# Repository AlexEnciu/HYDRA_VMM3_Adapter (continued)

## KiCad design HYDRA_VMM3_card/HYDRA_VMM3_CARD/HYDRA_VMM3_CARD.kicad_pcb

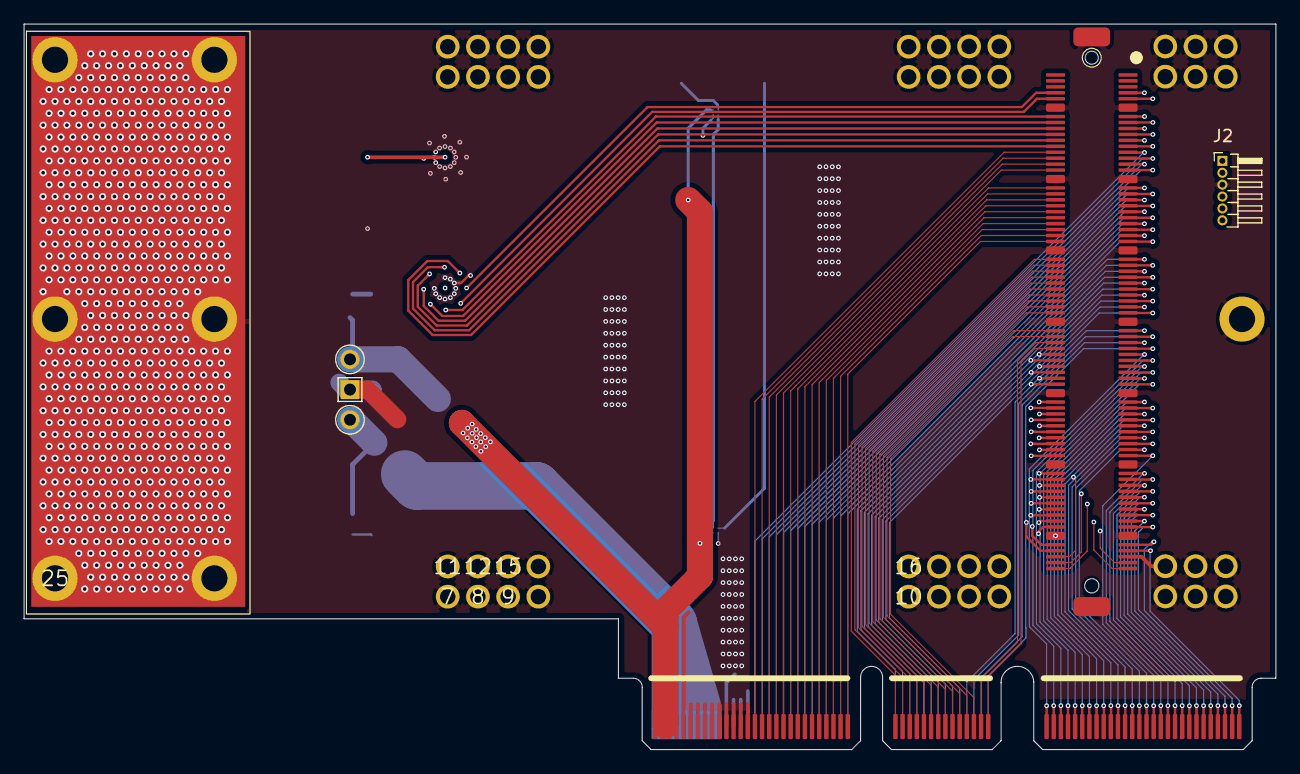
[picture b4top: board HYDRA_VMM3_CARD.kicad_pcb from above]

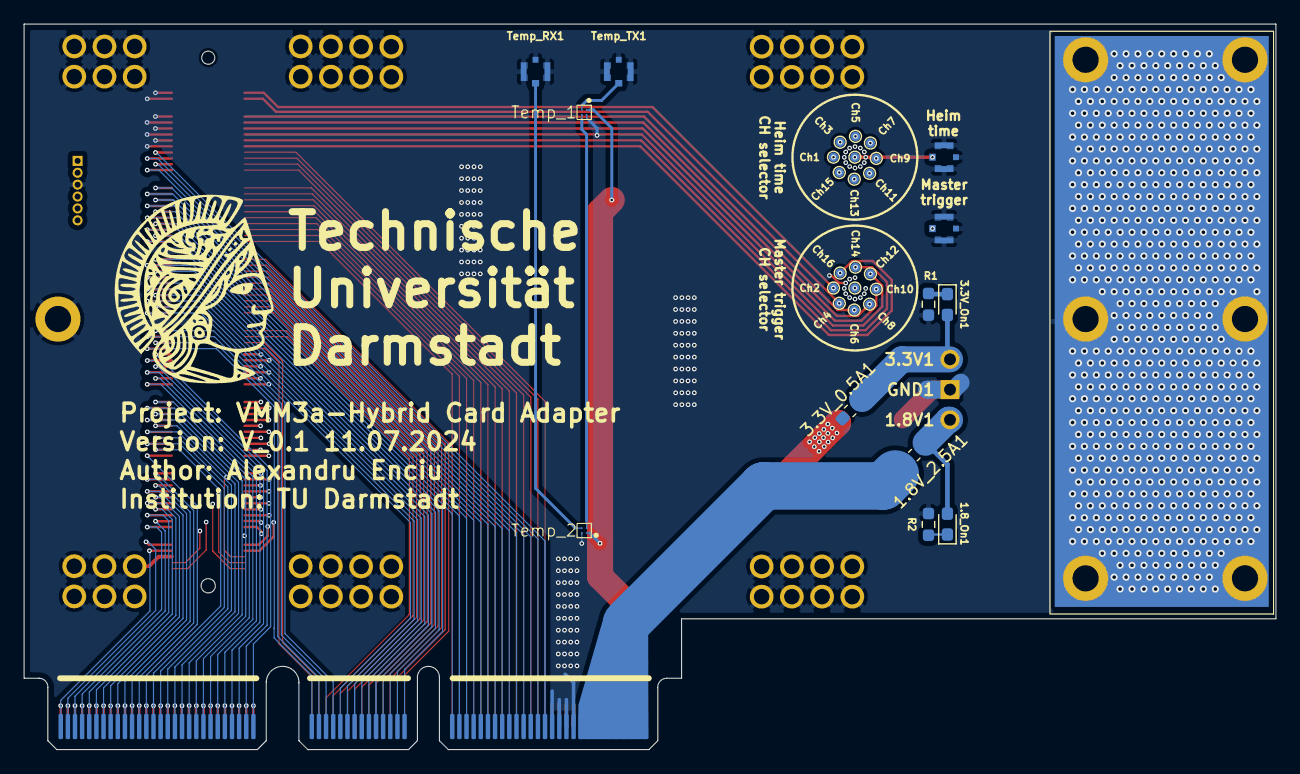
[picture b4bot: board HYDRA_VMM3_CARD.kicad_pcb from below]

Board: 6 copper layers, 105.3 x 61.0 mm, 61 parts (30 on the bottom side), 145 nets.

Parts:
1, 2, 3, 4, 5, 6, 7, 8, 9, 10, 11, 12, 13, 14, 15, 16, 17, 18, 19, 20, 21, 22, 23, 24, 25: (no value)
1.8V1: 1.8V; TestPoint_Pad_D2.5mm
1.8V_2.5A1: 2.5A; Fuse_0603_1608Metric_Pad1.05x0.95mm_HandSolder
1.8_On1, 3.3V_On1: LED; LED_0603_1608Metric_Pad1.05x0.95mm_HandSolder
3.3V1: 3.3V; TestPoint_Pad_D2.5mm
3.3V_0.5A1: 0.5A; Fuse_0603_1608Metric_Pad1.05x0.95mm_HandSolder
Ch1, Ch2, Ch3, Ch4, Ch5, Ch6, Ch7, Ch8, Ch9, Ch10, Ch11, Ch12, Ch13, Ch14, Ch15, Ch16: TestPoint; TestPoint_Pad_D1.0mm
GND1: GND; TestPoint_Pad_2.5x2.5mm
J1: ME1014010101011; Edge-Card-Connector
J2: Conn_01x06_Pin; PinHeader_1x06_P1.00mm_Horizontal
R1, R2: 1k; R_0603_1608Metric_Pad0.98x0.95mm_HandSolder
Sig1, Sig2: 20449-001E-03; IPEX_20449-001E-03
Sig1_selector, Sig2_selector: TestPoint; TestPoint_Pad_D1.0mm
Temp_1, Temp_2: TMP104
Temp_RX1: 20449-001E-03; IPEX_20449-001E-03
Temp_TX1: 20449-001E-03; IPEX_20449-001E-03
U1: Hirose-FX10

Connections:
Ch_1: Ch1.1, U1.7
Ch_2: Ch2.1, U1.8
Ch_3: Ch15.1, U1.9
Ch_4: Ch4.1, U1.10
Ch_5: Ch13.1, U1.11
Ch_6: Ch6.1, U1.12
Ch_7: Ch11.1, U1.13
Ch_8: Ch8.1, U1.14
Ch_9: Ch9.1, U1.15
Ch_10: Ch10.1, U1.16
Ch_11: Ch7.1, U1.17
Ch_12: Ch12.1, U1.18
Ch_13: Ch5.1, U1.19
Ch_14: Ch14.1, U1.20
Ch_15: Ch3.1, U1.21
Ch_16: Ch16.1, U1.22
Ch_17: J1.A15, U1.23
Ch_18: J1.B15, U1.24
Ch_19: J1.A16, U1.25
Ch_20: J1.B16, U1.26
Ch_21: J1.A17, U1.27
Ch_22: J1.B17, U1.28
Ch_23: J1.A18, U1.29
Ch_24: J1.B18, U1.30
Ch_25: J1.A19, U1.31
Ch_26: J1.B19, U1.32
Ch_27: J1.A20, U1.33
Ch_28: J1.B20, U1.34
Ch_29: J1.A21, U1.35
Ch_30: J1.B21, U1.36
Ch_31: J1.A22, U1.37
Ch_32: J1.B22, U1.38
Ch_33: J1.A23, U1.39
Ch_34: J1.B23, U1.40
Ch_35: J1.A24, U1.41
Ch_36: J1.B24, U1.42
Ch_37: J1.A25, U1.43
Ch_38: J1.B25, U1.44
Ch_39: J1.A26, U1.45
Ch_40: J1.B26, U1.46
Ch_41: J1.A27, U1.47
Ch_42: J1.B27, U1.48
Ch_43: J1.A28, U1.49
Ch_44: J1.B28, U1.50
Ch_45: J1.A29, U1.51
Ch_46: J1.B29, U1.52
Ch_47: J1.A30, U1.53
Ch_48: J1.B30, U1.54
Ch_49: J1.A31, U1.55
Ch_50: J1.B31, U1.56
Ch_51: J1.A32, U1.57
Ch_52: J1.B32, U1.58
Ch_53: J1.A33, U1.59
Ch_54: J1.B33, U1.60
Ch_55: J1.A34, U1.61
Ch_56: J1.B34, U1.62
Ch_57: J1.A35, U1.63
Ch_58: J1.B35, U1.64
Ch_59: J1.A36, U1.65
Ch_60: J1.B36, U1.66
Ch_61: J1.A37, U1.67
Ch_62: J1.B37, U1.68
Ch_63: J1.A38, U1.69
Ch_64: J1.B38, U1.70
Ch_65: J1.A39, U1.71
Ch_66: J1.B39, U1.72
Ch_67: J1.A40, U1.73
Ch_68: J1.B40, U1.74
Ch_69: J1.A41, U1.75
Ch_70: J1.B41, U1.76
Ch_71: J1.A42, U1.77
Ch_72: J1.B42, U1.78
Ch_73: J1.A43, U1.79
Ch_74: J1.B43, U1.80
Ch_75: J1.A44, U1.81
Ch_76: J1.B44, U1.82
Ch_77: J1.A45, U1.83
Ch_78: J1.B45, U1.84
Ch_79: J1.A46, U1.85
Ch_80: J1.B46, U1.86
Ch_81: J1.A47, U1.87
Ch_82: J1.B47, U1.88
Ch_83: J1.A48, U1.89
Ch_84: J1.B48, U1.90
Ch_85: J1.A49, U1.91
Ch_86: J1.B49, U1.92
Ch_87: J1.A50, U1.93
Ch_88: J1.B50, U1.94
Ch_89: J1.A51, U1.95
Ch_90: J1.B51, U1.96
Ch_91: J1.A52, U1.97
Ch_92: J1.B52, U1.98
Ch_93: J1.A53, U1.99
Ch_94: J1.B53, U1.100
Ch_95: J1.A54, U1.101
Ch_96: J1.B54, U1.102
Ch_97: J1.A55, U1.103
Ch_98: J1.B55, U1.104
Ch_99: J1.A56, U1.105
Ch_100: J1.B56, U1.106
Ch_101: J1.A57, U1.107
Ch_102: J1.B57, U1.108
Ch_103: J1.A58, U1.109
Ch_104: J1.B58, U1.110
Ch_105: J1.A59, U1.111
Ch_106: J1.B59, U1.112
Ch_107: J1.A60, U1.113
Ch_108: J1.B70, U1.114
Ch_109: J1.A61, U1.115
Ch_110: J1.B69, U1.116
Ch_111: J1.A62, U1.117
Ch_112: J1.B68, U1.118
Ch_113: J1.A63, U1.119
Ch_114: J1.B67, U1.120
Ch_115: J1.A64, U1.121
Ch_116: J1.B66, U1.122
Ch_117: J1.A65, U1.123
Ch_118: J1.B65, U1.124
Ch_119: J1.A66, U1.125
Ch_120: J1.B64, U1.126
Ch_121: J1.A67, U1.127
Ch_122: J1.B63, U1.128
Ch_123: J1.A68, U1.129
Ch_124: J1.B62, U1.130
Ch_125: J1.A69, U1.131
Ch_126: J1.B61, U1.132
Ch_127: J1.A70, U1.133
Ch_128: J1.B60, U1.134
GND: 1.1, 2.1, 3.1, 4.1, 5.1, 6.1, 7.1, 8.1, 9.1, 10.1, 11.1, 12.1, 13.1, 14.1, 15.1, 16.1, 17.1, 18.1, 19.1, 20.1, 21.1, 22.1, 23.1, 24.1, 25.1, GND1.1, J1.A11, J1.A12, J1.A13, J1.A14, J1.B5, J1.B6, J1.B7, J1.B8, J1.B9, J1.B10, J1.B11, J1.B12, J1.B13, J1.B14, J2.3, R1.2, R2.2, Sig1.2, Sig1.3, Sig1.4, Sig2.2, Sig2.3, Sig2.4, Temp_1.2 (GND), Temp_2.2 (GND), Temp_RX1.2, Temp_RX1.3, Temp_RX1.4, Temp_TX1.2, Temp_TX1.3, Temp_TX1.4, U1.135, U1.141 (GND)
I2C_VCC: J2.1, U1.136
unnamed: 1.8V1.1, 1.8V_2.5A1.2, 1.8_On1.2 (A)
unnamed: 1.8_On1.1 (K), R2.1
unnamed: 3.3V1.1, 3.3V_0.5A1.2, 3.3V_On1.2 (A)
unnamed: 3.3V_On1.1 (K), R1.1
unnamed: Temp_1.4 (RX), Temp_2.3 (TX)
P1: 3.3V_0.5A1.1, J1.B1, J1.B2, J1.B3, J1.B4, Temp_1.1 (V+), Temp_2.1 (V+)
P2: 1.8V_2.5A1.1, J1.A1, J1.A2, J1.A3, J1.A4, J1.A5, J1.A6, J1.A7, J1.A8, J1.A9, J1.A10
RX: Temp_2.4 (RX), Temp_RX1.1
SCL: J2.4, U1.140
SDA: J2.5, U1.139
Sig1: Sig1.1, Sig1_selector.1
Sig2: Sig2.1, Sig2_selector.1
Signal_In: J2.6, U1.137
Signal_Out: J2.2, U1.138
TX: Temp_1.3 (TX), Temp_TX1.1

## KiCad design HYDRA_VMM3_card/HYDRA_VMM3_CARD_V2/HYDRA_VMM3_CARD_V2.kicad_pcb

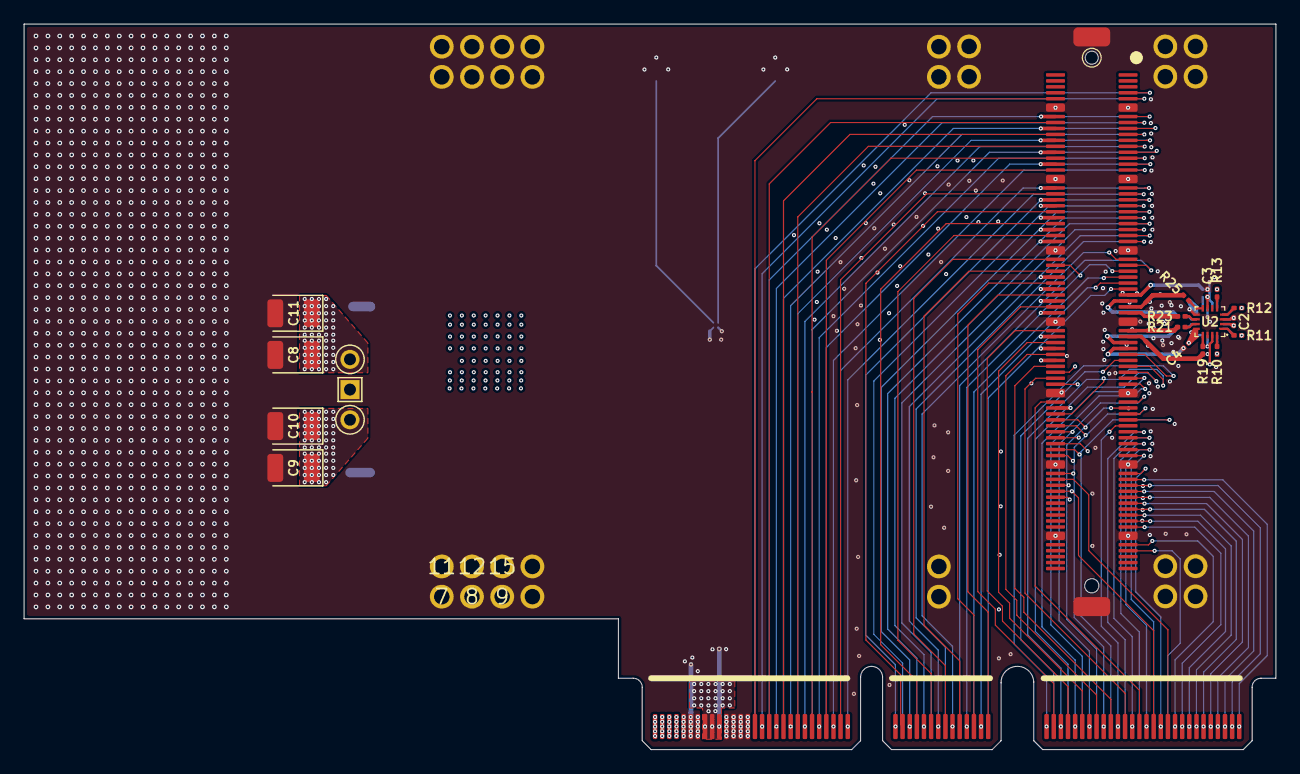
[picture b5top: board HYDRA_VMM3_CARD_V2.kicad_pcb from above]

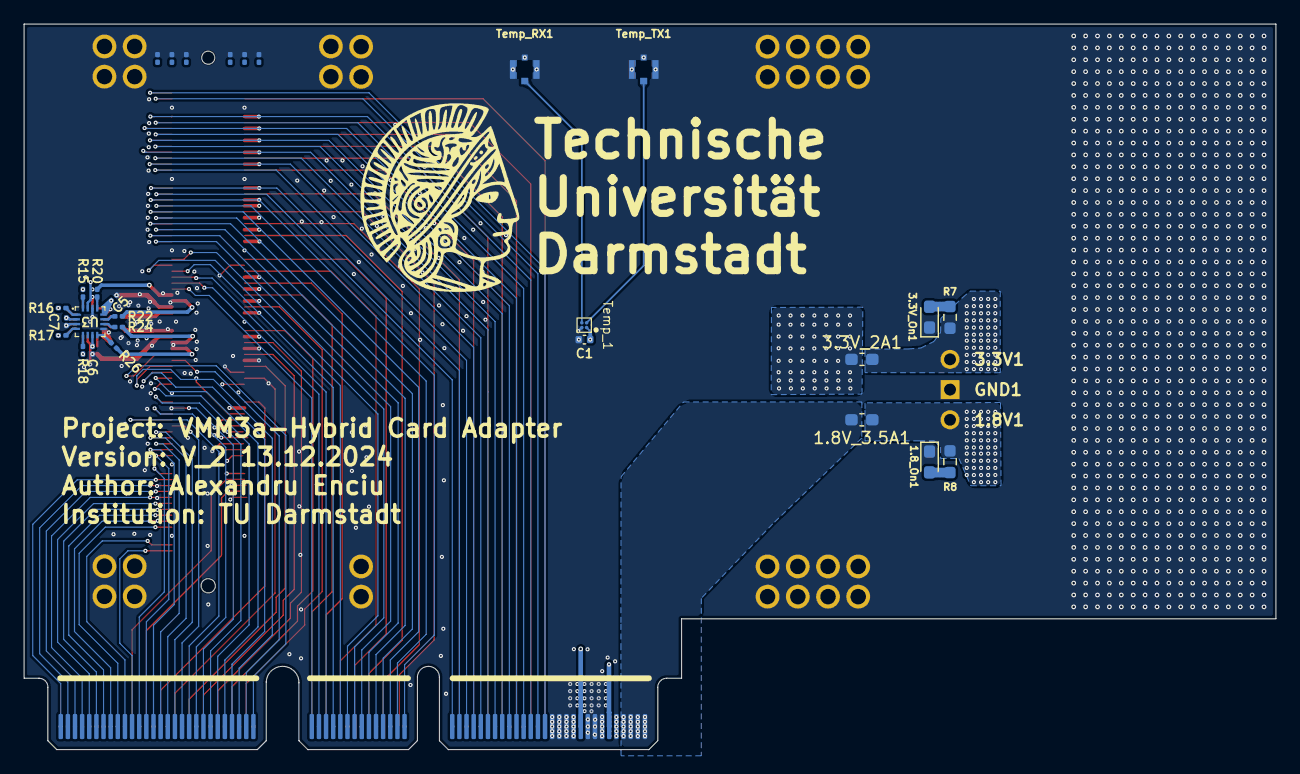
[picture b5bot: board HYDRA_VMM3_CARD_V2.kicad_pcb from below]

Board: 8 copper layers, 105.3 x 61.0 mm, 65 parts (28 on the bottom side), 153 nets.

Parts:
1, 2, 4, 5, 7, 8, 9, 11, 12, 13, 14, 15, 17, 20, 23, 24: (no value)
1.8V1: 1.8V; TestPoint_Pad_D2.5mm
1.8V_3.5A1: 2.5A; Fuse_0603_1608Metric_Pad1.05x0.95mm_HandSolder
1.8_On1, 3.3V_On1: LED; LED_0603_1608Metric_Pad1.05x0.95mm_HandSolder
3.3V1: 3.3V; TestPoint_Pad_D2.5mm
3.3V_2A1: 2A; Fuse_0603_1608Metric_Pad1.05x0.95mm_HandSolder
C1: 100nF; C_0402_1005Metric
C2, C3, C4, C5, C6, C7: 10nF; C_0201_0603Metric
C8, C9, C10, C11: TCJB475M025R0100; CP_EIA-3528-12_Kemet-T
GND1: GND; TestPoint_Pad_2.5x2.5mm
J1: ME1014010101011; Edge-Card-Connector
R1, R2, R3, R4, R5, R6: 10k; R_0201_0603Metric
R7, R8: 1k; R_0603_1608Metric_Pad0.98x0.95mm_HandSolder
R10, R11, R12, R13, R15, R16, R17, R18: 0; R_0201_0603Metric
R19, R20, R21, R22, R23, R24, R25, R26: 33; R_0201_0603Metric
Temp_1: TMP104
Temp_RX1: 20449-001E-03; IPEX_20449-001E-03
Temp_TX1: 20449-001E-03; IPEX_20449-001E-03
U1: Hirose-FX10
U2, U3: 5PB1214CMGK8

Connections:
/Heimtime/Enable_1: R15.2, U3.16 (OE_1)
/Heimtime/Enable_2: R16.2, U3.1 (OE_2)
/Heimtime/Enable_3: R17.2, U3.4 (OE_3)
/Heimtime/Enable_4: R18.2, U3.5 (OE_4)
/Master_trigg/Enable_1: R10.2, U2.16 (OE_1)
/Master_trigg/Enable_2: R11.2, U2.1 (OE_2)
/Master_trigg/Enable_3: R12.2, U2.4 (OE_3)
/Master_trigg/Enable_4: R13.2, U2.5 (OE_4)
Ch_1: J1.A15, U1.7
Ch_3: J1.A16, U1.9
Ch_4: J1.B15, U1.10
Ch_5: J1.A17, U1.11
Ch_6: J1.B16, U1.12
Ch_7: J1.A18, U1.13
Ch_8: J1.B17, U1.14
Ch_9: J1.A19, U1.15
Ch_10: J1.B18, U1.16
Ch_11: J1.A20, U1.17
Ch_12: J1.B19, U1.18
Ch_13: J1.A21, U1.19
Ch_14: J1.B20, U1.20
Ch_15: J1.A22, U1.21
Ch_16: J1.B21, U1.22
Ch_17: J1.A23, U1.23
Ch_18: J1.B22, U1.24
Ch_19: J1.A24, U1.25
Ch_20: J1.B23, U1.26
Ch_21: J1.A25, U1.27
Ch_22: J1.B24, U1.28
Ch_23: J1.A26, U1.29
Ch_24: J1.B25, U1.30
Ch_25: J1.A27, U1.31
Ch_26: J1.B26, U1.32
Ch_27: J1.A28, U1.33
Ch_28: J1.B27, U1.34
Ch_29: J1.A29, U1.35
Ch_30: J1.B28, U1.36
Ch_31: J1.A30, U1.37
Ch_32: J1.B29, U1.38
Ch_33: J1.A31, U1.39
Ch_34: J1.B30, U1.40
Ch_35: J1.A32, U1.41
Ch_36: J1.B31, U1.42
Ch_37: J1.A33, U1.43
Ch_38: J1.B32, U1.44
Ch_39: J1.A34, U1.45
Ch_40: J1.B33, U1.46
Ch_41: J1.A35, U1.47
Ch_42: J1.B34, U1.48
Ch_43: J1.A36, U1.49
Ch_44: J1.B35, U1.50
Ch_45: J1.A37, U1.51
Ch_46: J1.B36, U1.52
Ch_47: J1.A38, U1.53
Ch_48: J1.B37, U1.54
Ch_49: J1.A39, U1.55
Ch_50: J1.B38, U1.56
Ch_51: J1.A40, U1.57
Ch_52: J1.B39, U1.58
Ch_53: J1.A41, U1.59
Ch_54: J1.B40, U1.60
Ch_55: J1.A42, U1.61
Ch_56: J1.B41, U1.62
Ch_57: R20.2, U1.63
Ch_58: J1.B42, U1.64
Ch_59: R22.2, U1.65
Ch_60: J1.B43, U1.66
Ch_61: R25.2, U1.67
Ch_62: J1.B44, U1.68
Ch_63: R23.2, U1.69
Ch_64: J1.B45, U1.70
Ch_65: R21.2, U1.71
Ch_66: J1.B46, U1.72
Ch_67: R19.2, U1.73
Ch_68: J1.B47, U1.74
Ch_69: R24.2, U1.75
Ch_70: J1.B48, U1.76
Ch_71: R26.2, U1.77
Ch_72: J1.B49, U1.78
Ch_73: J1.A43, U1.79
Ch_74: J1.B50, U1.80
Ch_75: J1.A44, U1.81
Ch_76: J1.B51, U1.82
Ch_77: J1.A45, U1.83
Ch_78: J1.B52, U1.84
Ch_79: J1.A46, U1.85
Ch_80: J1.B53, U1.86
Ch_81: J1.A47, U1.87
Ch_82: J1.B54, U1.88
Ch_83: J1.A48, U1.89
Ch_84: J1.B55, U1.90
Ch_85: J1.A49, U1.91
Ch_86: J1.B56, U1.92
Ch_87: J1.A50, U1.93
Ch_88: J1.B70, U1.94
Ch_89: J1.A51, U1.95
Ch_90: J1.B69, U1.96
Ch_91: J1.A52, U1.97
Ch_92: J1.B68, U1.98
Ch_93: J1.A53, U1.99
Ch_94: J1.B67, U1.100
Ch_95: J1.A54, U1.101
Ch_96: J1.B66, U1.102
Ch_97: J1.A55, U1.103
Ch_98: J1.B65, U1.104
Ch_99: J1.A56, U1.105
Ch_100: J1.B64, U1.106
Ch_101: J1.A57, U1.107
Ch_102: J1.B63, U1.108
Ch_103: J1.A58, U1.109
Ch_104: J1.B62, U1.110
Ch_105: J1.A59, U1.111
Ch_106: J1.B61, U1.112
Ch_107: J1.A70, U1.113
Ch_108: J1.B60, U1.114
Ch_109: J1.A69, U1.115
Ch_110: J1.B59, U1.116
Ch_111: J1.A68, U1.117
Ch_112: J1.B58, U1.118
Ch_113: J1.A67, U1.119
Ch_114: J1.B57, U1.120
Ch_115: J1.A66, U1.121
Ch_117: J1.A65, U1.123
Ch_119: J1.A64, U1.125
Ch_121: J1.A63, U1.127
Ch_123: J1.A62, U1.129
Ch_125: J1.A61, U1.131
Ch_127: J1.A60, U1.133
GND: 1.1, 1.8_On1.1 (K), 2.1, 3.3V_On1.1 (K), 4.1, 5.1, 7.1, 8.1, 9.1, 11.1, 12.1, 13.1, 14.1, 15.1, 17.1, 20.1, 23.1, 24.1, C1.2, C2.1, C3.1, C4.1, C5.1, C6.1, C7.1, C8.2, C9.2, C10.2, C11.2, GND1.1, J1.A5, J1.A7, J1.A8, J1.A9, J1.A11, J1.A12, J1.A13, J1.A14, J1.B5, J1.B6, J1.B7, J1.B11, J1.B12, J1.B13, J1.B14, R1.2, R2.2, R3.2, R4.2, R5.2, R6.2, Temp_1.2 (GND), Temp_RX1.2, Temp_RX1.3, Temp_RX1.4, Temp_TX1.2, Temp_TX1.3, Temp_TX1.4, U1.141 (GND), U2.3 (GND), U2.9 (GND), U2.14 (GND), U3.3 (GND), U3.9 (GND), U3.14 (GND)
Heimtime: J1.A10, U3.15 (CLK_IN)
Master_Trigg: J1.A6, U2.15 (CLK_IN)
unnamed: 1.8_On1.2 (A), R8.2
unnamed: 3.3V_On1.2 (A), R7.2
unnamed: R19.1, U2.13 (CLK_OUT1)
unnamed: R21.1, U2.11 (CLK_OUT2)
unnamed: R23.1, U2.10 (CLK_OUT3)
unnamed: R25.1, U2.8 (CLK_OUT4)
unnamed: R20.1, U3.13 (CLK_OUT1)
unnamed: R22.1, U3.11 (CLK_OUT2)
unnamed: R24.1, U3.10 (CLK_OUT3)
unnamed: R26.1, U3.8 (CLK_OUT4)
P1: 3.3V_2A1.1, C1.1, C2.2, C3.2, C4.2, C5.2, C6.2, C7.2, J1.B8, J1.B9, J1.B10, R10.1, R11.1, R12.1, R13.1, R15.1, R16.1, R17.1, R18.1, Temp_1.1 (V+), U2.2 (VDD), U2.7 (VDD), U2.12 (VDD), U3.2 (VDD), U3.7 (VDD), U3.12 (VDD)
P1_Out: 3.3V1.1, 3.3V_2A1.2, C8.1, C11.1, R7.1
P2: 1.8V_3.5A1.1, J1.A1, J1.A2, J1.A3, J1.A4, J1.B1, J1.B2, J1.B3, J1.B4
P2_Out: 1.8V1.1, 1.8V_3.5A1.2, C9.1, C10.1, R8.1
RX: Temp_1.4 (RX), Temp_RX1.1
TX: Temp_1.3 (TX), Temp_TX1.1
bit_0: R1.1, U1.1
bit_1: R2.1, U1.2
bit_2: R3.1, U1.3
bit_3: R4.1, U1.4
bit_4: R5.1, U1.5
bit_5: R6.1, U1.6

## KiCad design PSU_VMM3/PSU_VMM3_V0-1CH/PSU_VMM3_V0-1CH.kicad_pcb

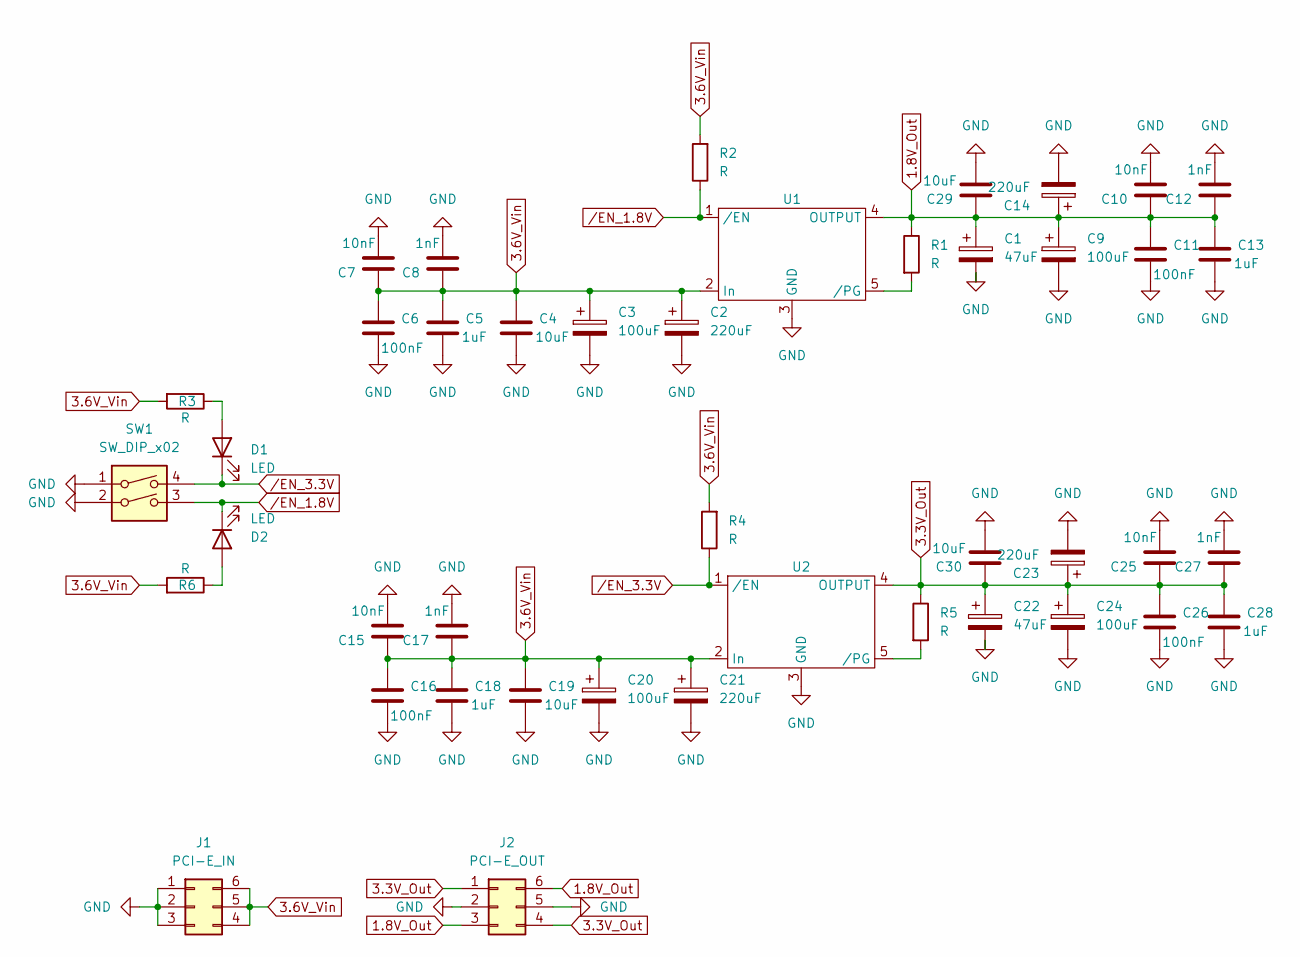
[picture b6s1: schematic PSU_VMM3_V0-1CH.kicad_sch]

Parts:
C1, C22: 47uF; CP_Elec_5x5.4
C2, C14, C21, C23: 220uF; CP_Elec_8x10.5
C3, C9, C20, C24: 100uF; CP_Elec_8x6.2
C4, C19, C29, C30: 10uF; C_0805_2012Metric
C5, C13, C18, C28: 1uF; C_0805_2012Metric
C6, C11, C16, C26: 100nF; C_0603_1608Metric
C7, C10, C15, C25: 10nF; C_0603_1608Metric
C8, C12, C17, C27: 1nF; C_0603_1608Metric
D1, D2: LED; LED_0603_1608Metric
J1: PCI-E_IN; MOLEX_39-30-1060
J2: PCI-E_OUT; MOLEX_39-30-1060
R1, R2, R3, R4, R5, R6: R; R_0603_1608Metric
SW1: SW_DIP_x02; SW_DIP_SPSTx02_Slide_6.7x6.64mm_W8.61mm_P2.54mm_LowProfile
U1, U2: TO-263-5_TabPin3

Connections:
1.8V_Out: C1.1, C9.1, C10.1, C11.1, C12.1, C13.1, C14.1, C29.1, J2.3, J2.6, R1.1, U1.4 (OUTPUT)
3.3V_Out: C22.1, C23.1, C24.1, C25.1, C26.1, C27.1, C28.1, C30.1, J2.1, J2.4, R5.1, U2.4 (OUTPUT)
3.6V_Vin: C2.1, C3.1, C4.1, C5.1, C6.1, C7.1, C8.1, C15.1, C16.1, C17.1, C18.1, C19.1, C20.1, C21.1, J1.4, J1.5, J1.6, R2.2, R3.2, R4.2, R6.2, U1.2 (In), U2.2 (In)
GND: C1.2, C2.2, C3.2, C4.2, C5.2, C6.2, C7.2, C8.2, C9.2, C10.2, C11.2, C12.2, C13.2, C14.2, C15.2, C16.2, C17.2, C18.2, C19.2, C20.2, C21.2, C22.2, C23.2, C24.2, C25.2, C26.2, C27.2, C28.2, C29.2, C30.2, J1.1, J1.2, J1.3, J2.2, J2.5, SW1.1, SW1.2, U1.3 (GND), U2.3 (GND)
unnamed: D1.2 (A), R3.1
unnamed: D2.2 (A), R6.1
unnamed: R1.2, U1.5 (/PG)
unnamed: R5.2, U2.5 (/PG)
/EN_1.8V: D2.1 (K), R2.1, SW1.3, U1.1 (/EN)
/EN_3.3V: D1.1 (K), R4.1, SW1.4, U2.1 (/EN)

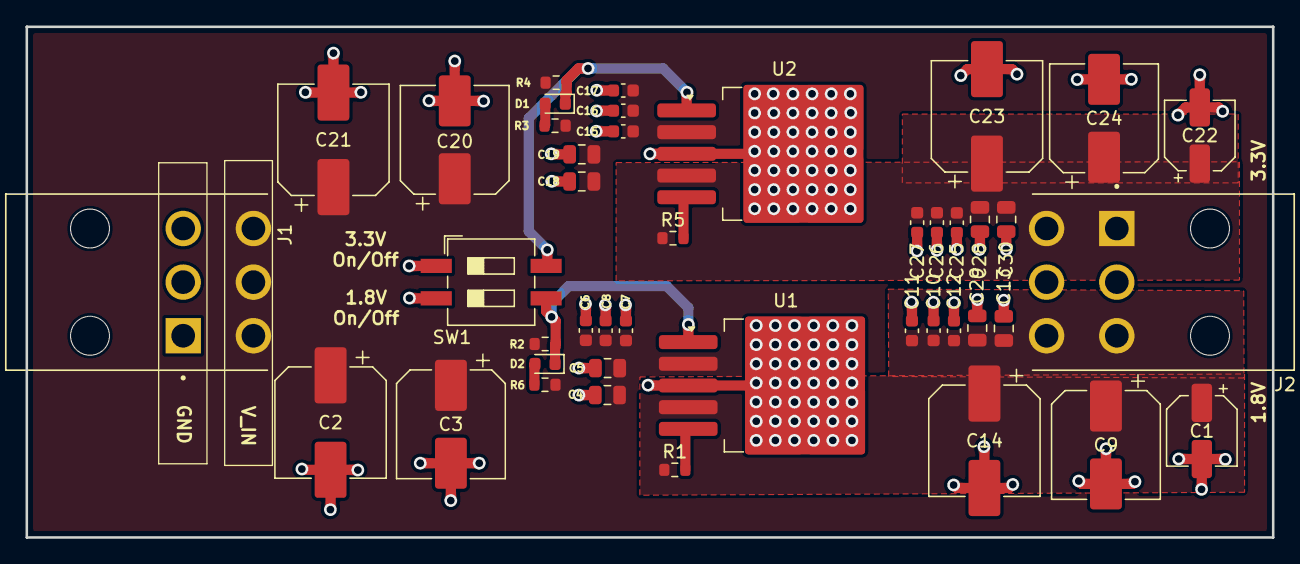
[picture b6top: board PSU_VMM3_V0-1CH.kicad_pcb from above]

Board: 4 copper layers, 97.6 x 40.0 mm, 43 parts (0 on the bottom side), 10 nets.

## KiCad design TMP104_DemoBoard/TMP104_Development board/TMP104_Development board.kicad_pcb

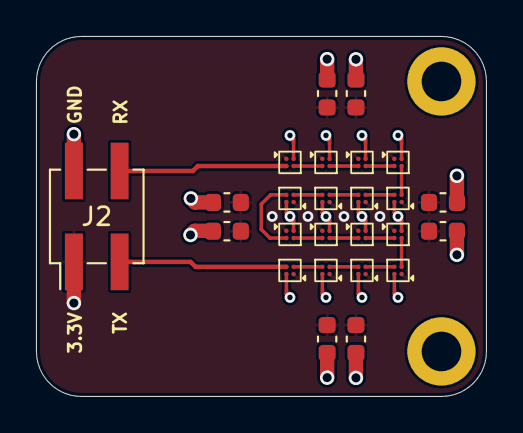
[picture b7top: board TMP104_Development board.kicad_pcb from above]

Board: 4 copper layers, 25.0 x 20.0 mm, 25 parts (0 on the bottom side), 19 nets.

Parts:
C1, C2, C3, C4, C5, C6, C7, C8: 0.1 uF; C_0603_1608Metric
J2: 95278-801A04LF; PinHeader_2x02_P2.54mm_Vertical_SMD
U2, U3, U4, U5, U6, U7, U8, U9, U10, U11, U12, U13, U14, U15, U16, U17: TMP104YFFR; TMP104

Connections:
GND: C1.2, C2.2, C3.2, C4.2, C5.2, C6.2, C7.2, C8.2, J2.2, U2.2 (GND), U3.2 (GND), U4.2 (GND), U5.2 (GND), U6.2 (GND), U7.2 (GND), U8.2 (GND), U9.2 (GND), U10.2 (GND), U11.2 (GND), U12.2 (GND), U13.2 (GND), U14.2 (GND), U15.2 (GND), U16.2 (GND), U17.2 (GND)
unnamed: U2.4 (RX), U3.3 (TX)
unnamed: U3.4 (RX), U4.3 (TX)
unnamed: U4.4 (RX), U5.3 (TX)
unnamed: U5.4 (RX), U6.3 (TX)
unnamed: U6.4 (RX), U7.3 (TX)
unnamed: U7.4 (RX), U8.3 (TX)
unnamed: U8.4 (RX), U9.3 (TX)
unnamed: U10.4 (RX), U17.3 (TX)
unnamed: U10.3 (TX), U11.4 (RX)
unnamed: U11.3 (TX), U12.4 (RX)
unnamed: U12.3 (TX), U13.4 (RX)
unnamed: U9.4 (RX), U13.3 (TX)
unnamed: U14.3 (TX), U15.4 (RX)
unnamed: U15.3 (TX), U16.4 (RX)
unnamed: U16.3 (TX), U17.4 (RX)
RX_2: J2.4, U2.3 (TX)
TX_2: J2.3, U14.4 (RX)
VCC_3.3V: C1.1, C2.1, C3.1, C4.1, C5.1, C6.1, C7.1, C8.1, J2.1, U2.1 (VCC), U3.1 (VCC), U4.1 (VCC), U5.1 (VCC), U6.1 (VCC), U7.1 (VCC), U8.1 (VCC), U9.1 (VCC), U10.1 (VCC), U11.1 (VCC), U12.1 (VCC), U13.1 (VCC), U14.1 (VCC), U15.1 (VCC), U16.1 (VCC), U17.1 (VCC)

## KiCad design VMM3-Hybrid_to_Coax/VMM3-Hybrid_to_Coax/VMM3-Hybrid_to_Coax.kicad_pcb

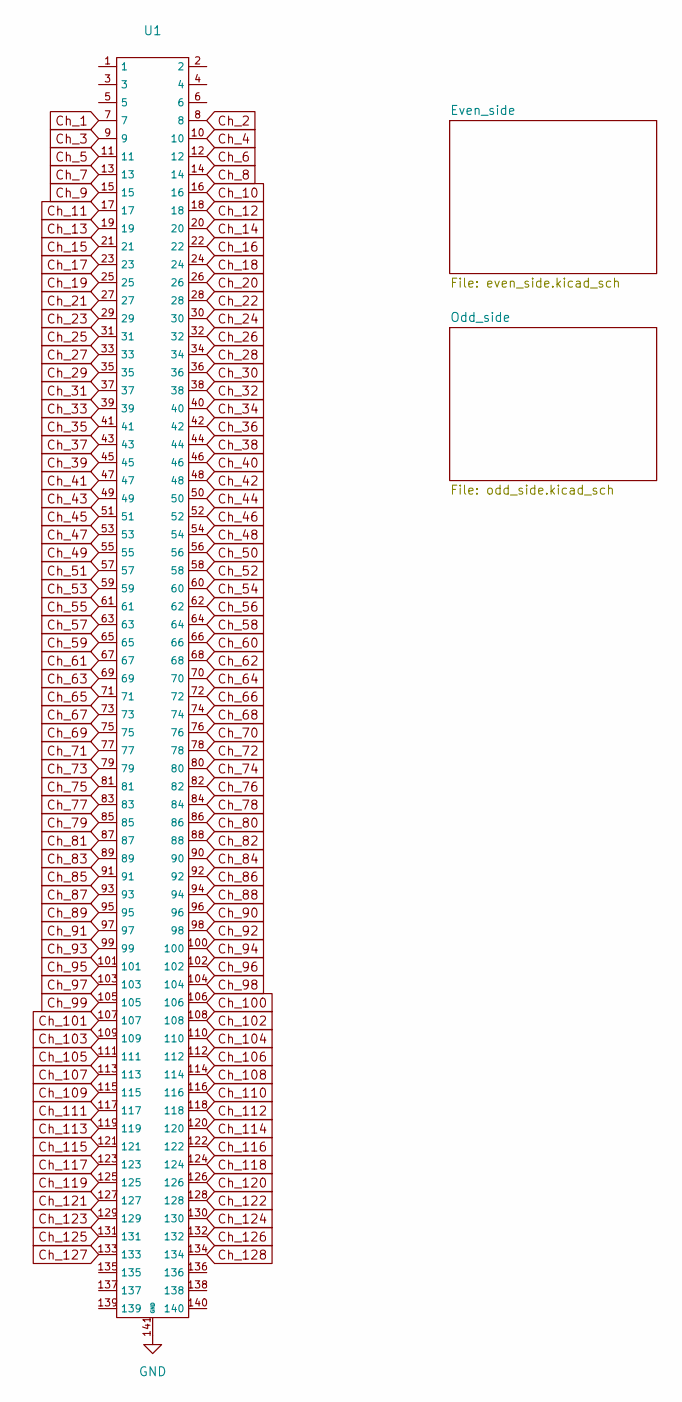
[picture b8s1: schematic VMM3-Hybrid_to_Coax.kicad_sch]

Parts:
U1: Hirose-FX10

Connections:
Ch_1: U1.7; also elsewhere on the board
Ch_2: U1.8; also elsewhere on the board
Ch_3: U1.9; also elsewhere on the board
Ch_4: U1.10; also elsewhere on the board
Ch_5: U1.11; also elsewhere on the board
Ch_6: U1.12; also elsewhere on the board
Ch_7: U1.13
Ch_8: U1.14
Ch_9: U1.15
Ch_10: U1.16
Ch_11: U1.17
Ch_12: U1.18
Ch_13: U1.19
Ch_14: U1.20
Ch_15: U1.21
Ch_16: U1.22
Ch_17: U1.23; also elsewhere on the board
Ch_18: U1.24; also elsewhere on the board
Ch_19: U1.25; also elsewhere on the board
Ch_20: U1.26; also elsewhere on the board
Ch_21: U1.27; also elsewhere on the board
Ch_22: U1.28; also elsewhere on the board
Ch_23: U1.29
Ch_24: U1.30
Ch_25: U1.31
Ch_26: U1.32
Ch_27: U1.33
Ch_28: U1.34
Ch_29: U1.35
Ch_30: U1.36
Ch_31: U1.37
Ch_32: U1.38
Ch_33: U1.39; also elsewhere on the board
Ch_34: U1.40; also elsewhere on the board
Ch_35: U1.41; also elsewhere on the board
Ch_36: U1.42; also elsewhere on the board
Ch_37: U1.43; also elsewhere on the board
Ch_38: U1.44; also elsewhere on the board
Ch_39: U1.45
Ch_40: U1.46
Ch_41: U1.47
Ch_42: U1.48
Ch_43: U1.49
Ch_44: U1.50
Ch_45: U1.51
Ch_46: U1.52
Ch_47: U1.53
Ch_48: U1.54
Ch_49: U1.55; also elsewhere on the board
Ch_50: U1.56; also elsewhere on the board
Ch_51: U1.57; also elsewhere on the board
Ch_52: U1.58; also elsewhere on the board
Ch_53: U1.59; also elsewhere on the board
Ch_54: U1.60; also elsewhere on the board
Ch_55: U1.61
Ch_56: U1.62
Ch_57: U1.63
Ch_58: U1.64
Ch_59: U1.65
Ch_60: U1.66
Ch_61: U1.67
Ch_62: U1.68
Ch_63: U1.69
Ch_64: U1.70
Ch_65: U1.71; also elsewhere on the board
Ch_66: U1.72; also elsewhere on the board
Ch_67: U1.73; also elsewhere on the board
Ch_68: U1.74; also elsewhere on the board
Ch_69: U1.75; also elsewhere on the board
Ch_70: U1.76; also elsewhere on the board
Ch_71: U1.77
Ch_72: U1.78
Ch_73: U1.79
Ch_74: U1.80
Ch_75: U1.81
Ch_76: U1.82
Ch_77: U1.83
Ch_78: U1.84
Ch_79: U1.85
Ch_80: U1.86
Ch_81: U1.87; also elsewhere on the board
Ch_82: U1.88; also elsewhere on the board
Ch_83: U1.89; also elsewhere on the board
Ch_84: U1.90; also elsewhere on the board
Ch_85: U1.91; also elsewhere on the board
Ch_86: U1.92; also elsewhere on the board
Ch_87: U1.93
Ch_88: U1.94
Ch_89: U1.95
Ch_90: U1.96
Ch_91: U1.97
Ch_92: U1.98
Ch_93: U1.99
Ch_94: U1.100
Ch_95: U1.101
Ch_96: U1.102
Ch_97: U1.103; also elsewhere on the board
Ch_98: U1.104; also elsewhere on the board
Ch_99: U1.105; also elsewhere on the board
Ch_100: U1.106; also elsewhere on the board
Ch_101: U1.107; also elsewhere on the board
Ch_102: U1.108; also elsewhere on the board
Ch_103: U1.109
Ch_104: U1.110
Ch_105: U1.111
Ch_106: U1.112
Ch_107: U1.113
Ch_108: U1.114
Ch_109: U1.115
Ch_110: U1.116
Ch_111: U1.117
Ch_112: U1.118
Ch_113: U1.119; also elsewhere on the board
Ch_114: U1.120; also elsewhere on the board
Ch_115: U1.121; also elsewhere on the board
Ch_116: U1.122; also elsewhere on the board
Ch_117: U1.123; also elsewhere on the board
Ch_118: U1.124; also elsewhere on the board
Ch_119: U1.125
Ch_120: U1.126
Ch_121: U1.127
Ch_122: U1.128
Ch_123: U1.129
Ch_124: U1.130
Ch_125: U1.131
Ch_126: U1.132
Ch_127: U1.133
Ch_128: U1.134
GND: U1.141 (GND); also elsewhere on the board

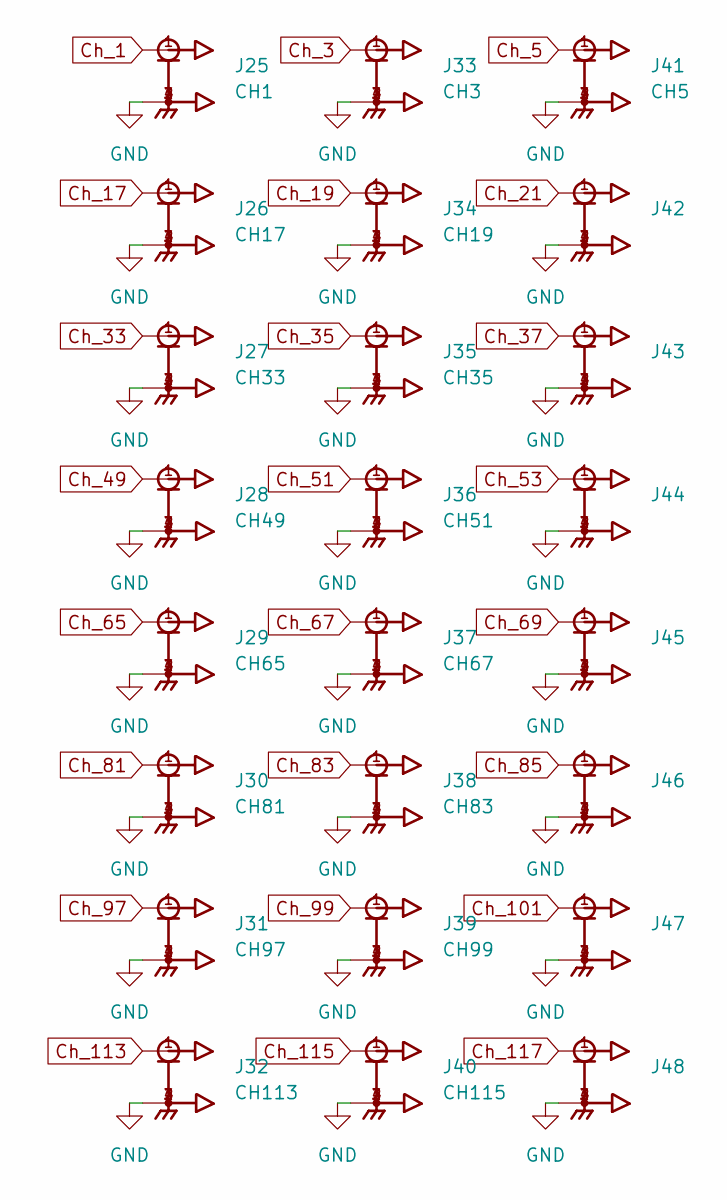
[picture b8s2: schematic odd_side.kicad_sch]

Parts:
J25: CH1; IPEX_20449-001E-03; PARTREV 5
J26: CH17; IPEX_20449-001E-03; PARTREV 5
J27: CH33; IPEX_20449-001E-03; PARTREV 5
J28: CH49; IPEX_20449-001E-03; PARTREV 5
J29: CH65; IPEX_20449-001E-03; PARTREV 5
J30: CH81; IPEX_20449-001E-03; PARTREV 5
J31: CH97; IPEX_20449-001E-03; PARTREV 5
J32: CH113; IPEX_20449-001E-03; PARTREV 5
J33: CH3; IPEX_20449-001E-03; PARTREV 5
J34: CH19; IPEX_20449-001E-03; PARTREV 5
J35: CH35; IPEX_20449-001E-03; PARTREV 5
J36: CH51; IPEX_20449-001E-03; PARTREV 5
J37: CH67; IPEX_20449-001E-03; PARTREV 5
J38: CH83; IPEX_20449-001E-03; PARTREV 5
J39: CH99; IPEX_20449-001E-03; PARTREV 5
J40: CH115; IPEX_20449-001E-03; PARTREV 5
J41: CH5; IPEX_20449-001E-03; PARTREV 5
J42: CH21; IPEX_20449-001E-03; PARTREV 5
J43: CH37; IPEX_20449-001E-03; PARTREV 5
J44: CH53; IPEX_20449-001E-03; PARTREV 5
J45: CH69; IPEX_20449-001E-03; PARTREV 5
J46: CH85; IPEX_20449-001E-03; PARTREV 5
J47: CH101; IPEX_20449-001E-03; PARTREV 5
J48: CH117; IPEX_20449-001E-03; PARTREV 5

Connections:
Ch_1: J25.1; also elsewhere on the board
Ch_3: J33.1; also elsewhere on the board
Ch_5: J41.1; also elsewhere on the board
Ch_17: J26.1; also elsewhere on the board
Ch_19: J34.1; also elsewhere on the board
Ch_21: J42.1; also elsewhere on the board
Ch_33: J27.1; also elsewhere on the board
Ch_35: J35.1; also elsewhere on the board
Ch_37: J43.1; also elsewhere on the board
Ch_49: J28.1; also elsewhere on the board
Ch_51: J36.1; also elsewhere on the board
Ch_53: J44.1; also elsewhere on the board
Ch_65: J29.1; also elsewhere on the board
Ch_67: J37.1; also elsewhere on the board
Ch_69: J45.1; also elsewhere on the board
Ch_81: J30.1; also elsewhere on the board
Ch_83: J38.1; also elsewhere on the board
Ch_85: J46.1; also elsewhere on the board
Ch_97: J31.1; also elsewhere on the board
Ch_99: J39.1; also elsewhere on the board
Ch_101: J47.1; also elsewhere on the board
Ch_113: J32.1; also elsewhere on the board
Ch_115: J40.1; also elsewhere on the board
Ch_117: J48.1; also elsewhere on the board
GND: J25.2, J25.3, J25.4, J26.2, J26.3, J26.4, J27.2, J27.3, J27.4, J28.2, J28.3, J28.4, J29.2, J29.3, J29.4, J30.2, J30.3, J30.4, J31.2, J31.3, J31.4, J32.2, J32.3, J32.4, J33.2, J33.3, J33.4, J34.2, J34.3, J34.4, J35.2, J35.3, J35.4, J36.2, J36.3, J36.4, J37.2, J37.3, J37.4, J38.2, J38.3, J38.4, J39.2, J39.3, J39.4, J40.2, J40.3, J40.4, J41.2, J41.3, J41.4, J42.2, J42.3, J42.4, J43.2, J43.3, J43.4, J44.2, J44.3, J44.4, J45.2, J45.3, J45.4, J46.2, J46.3, J46.4, J47.2, J47.3, J47.4, J48.2, J48.3, J48.4; also elsewhere on the board

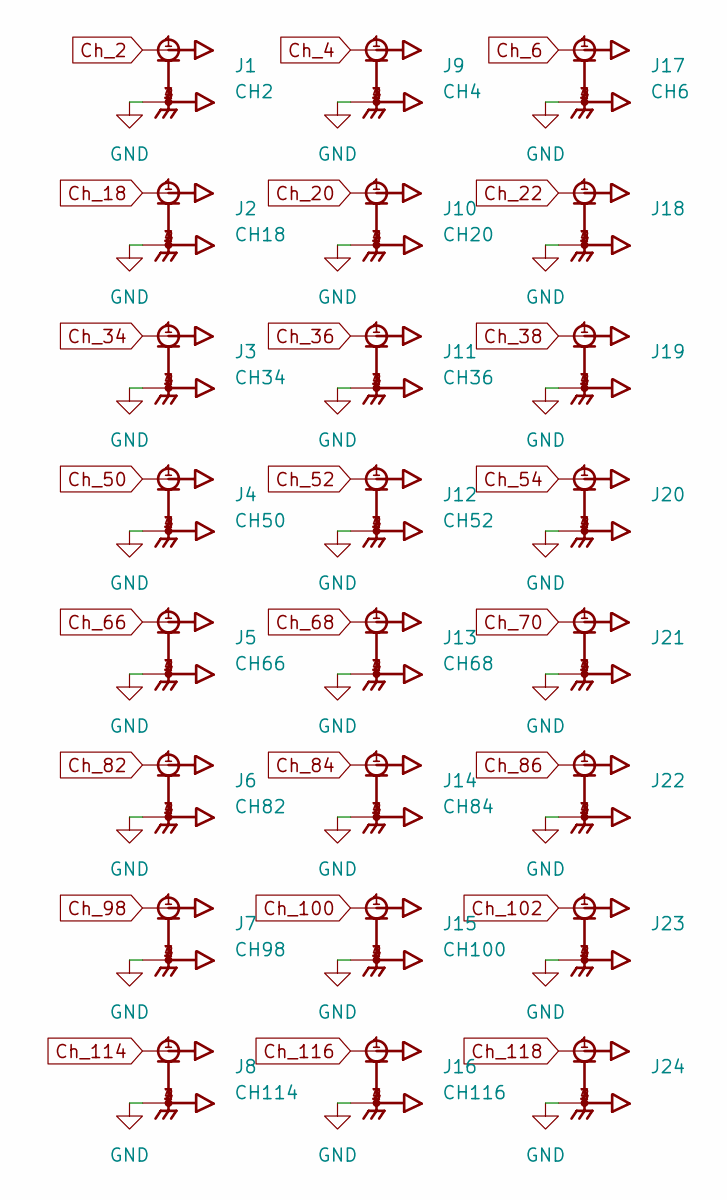
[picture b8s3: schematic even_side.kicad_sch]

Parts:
J1: CH2; IPEX_20449-001E-03; PARTREV 5
J2: CH18; IPEX_20449-001E-03; PARTREV 5
J3: CH34; IPEX_20449-001E-03; PARTREV 5
J4: CH50; IPEX_20449-001E-03; PARTREV 5
J5: CH66; IPEX_20449-001E-03; PARTREV 5
J6: CH82; IPEX_20449-001E-03; PARTREV 5
J7: CH98; IPEX_20449-001E-03; PARTREV 5
J8: CH114; IPEX_20449-001E-03; PARTREV 5
J9: CH4; IPEX_20449-001E-03; PARTREV 5
J10: CH20; IPEX_20449-001E-03; PARTREV 5
J11: CH36; IPEX_20449-001E-03; PARTREV 5
J12: CH52; IPEX_20449-001E-03; PARTREV 5
J13: CH68; IPEX_20449-001E-03; PARTREV 5
J14: CH84; IPEX_20449-001E-03; PARTREV 5
J15: CH100; IPEX_20449-001E-03; PARTREV 5
J16: CH116; IPEX_20449-001E-03; PARTREV 5
J17: CH6; IPEX_20449-001E-03; PARTREV 5
J18: CH22; IPEX_20449-001E-03; PARTREV 5
J19: CH38; IPEX_20449-001E-03; PARTREV 5
J20: CH54; IPEX_20449-001E-03; PARTREV 5
J21: CH70; IPEX_20449-001E-03; PARTREV 5
J22: CH86; IPEX_20449-001E-03; PARTREV 5
J23: CH102; IPEX_20449-001E-03; PARTREV 5
J24: CH118; IPEX_20449-001E-03; PARTREV 5

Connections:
Ch_2: J1.1; also elsewhere on the board
Ch_4: J9.1; also elsewhere on the board
Ch_6: J17.1; also elsewhere on the board
Ch_18: J2.1; also elsewhere on the board
Ch_20: J10.1; also elsewhere on the board
Ch_22: J18.1; also elsewhere on the board
Ch_34: J3.1; also elsewhere on the board
Ch_36: J11.1; also elsewhere on the board
Ch_38: J19.1; also elsewhere on the board
Ch_50: J4.1; also elsewhere on the board
Ch_52: J12.1; also elsewhere on the board
Ch_54: J20.1; also elsewhere on the board
Ch_66: J5.1; also elsewhere on the board
Ch_68: J13.1; also elsewhere on the board
Ch_70: J21.1; also elsewhere on the board
Ch_82: J6.1; also elsewhere on the board
Ch_84: J14.1; also elsewhere on the board
Ch_86: J22.1; also elsewhere on the board
Ch_98: J7.1; also elsewhere on the board
Ch_100: J15.1; also elsewhere on the board
Ch_102: J23.1; also elsewhere on the board
Ch_114: J8.1; also elsewhere on the board
Ch_116: J16.1; also elsewhere on the board
Ch_118: J24.1; also elsewhere on the board
GND: J1.2, J1.3, J1.4, J2.2, J2.3, J2.4, J3.2, J3.3, J3.4, J4.2, J4.3, J4.4, J5.2, J5.3, J5.4, J6.2, J6.3, J6.4, J7.2, J7.3, J7.4, J8.2, J8.3, J8.4, J9.2, J9.3, J9.4, J10.2, J10.3, J10.4, J11.2, J11.3, J11.4, J12.2, J12.3, J12.4, J13.2, J13.3, J13.4, J14.2, J14.3, J14.4, J15.2, J15.3, J15.4, J16.2, J16.3, J16.4, J17.2, J17.3, J17.4, J18.2, J18.3, J18.4, J19.2, J19.3, J19.4, J20.2, J20.3, J20.4, J21.2, J21.3, J21.4, J22.2, J22.3, J22.4, J23.2, J23.3, J23.4, J24.2, J24.3, J24.4; also elsewhere on the board
